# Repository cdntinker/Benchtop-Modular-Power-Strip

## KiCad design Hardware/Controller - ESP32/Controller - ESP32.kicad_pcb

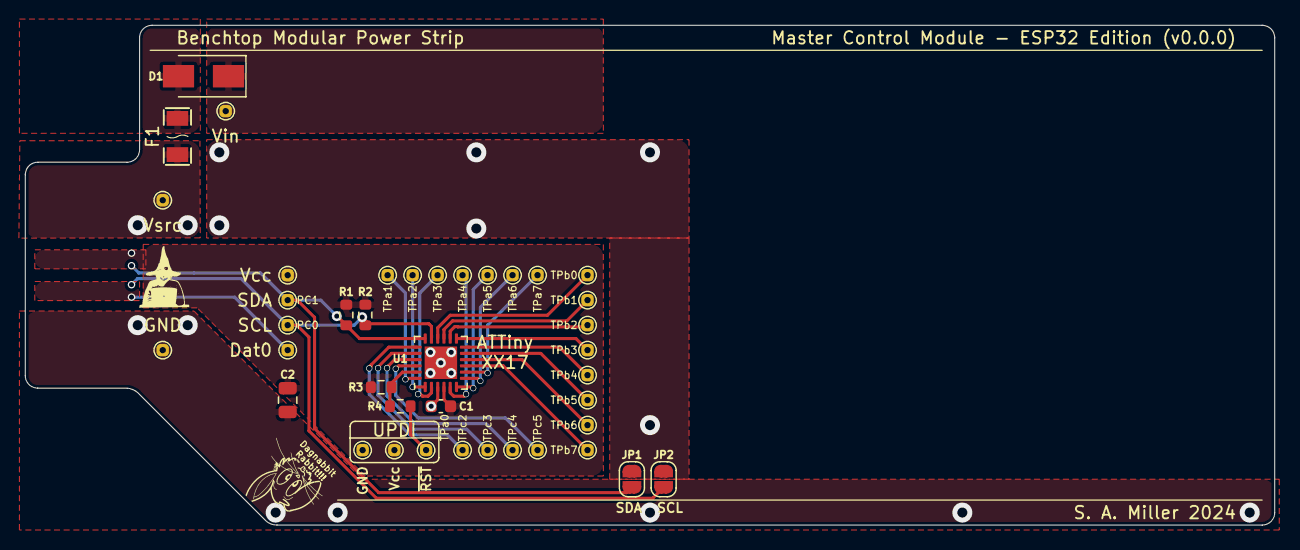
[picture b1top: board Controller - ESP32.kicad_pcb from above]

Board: 2 copper layers, 100.0 x 40.0 mm, 40 parts (0 on the bottom side), 28 nets.

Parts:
C1: 100nF; C_0603_1608Metric
C2: 4.7uF; C_0805_2012Metric
D1: D_Schottky; D_SMA
F1: Polyfuse; F1206
JP1, JP2: SolderJumper_2_Open; SolderJumper-2_P1.3mm_Open_RoundedPad1.0x1.5mm
R1, R2, R3: 10k; R_0603_1608Metric
R4: 330R; R_0603_1608Metric
TP1: Vsrc; TestPoint_THTPad_D1.0mm_Drill0.5mm
TP2, TP9: GND; TestPoint_THTPad_D1.0mm_Drill0.5mm
TP3: Dat0; TestPoint_THTPad_D1.0mm_Drill0.5mm
TP4: Dat1; TestPoint_THTPad_D1.0mm_Drill0.5mm
TP5: Dat2; TestPoint_THTPad_D1.0mm_Drill0.5mm
TP6: Dat3; TestPoint_THTPad_D1.0mm_Drill0.5mm
TP7: Vin; TestPoint_THTPad_D1.0mm_Drill0.5mm
TP8: I2C-Vcc; TestPoint_THTPad_D1.0mm_Drill0.5mm
TPa0: ~{RESET}; TestPoint_THTPad_D1.0mm_Drill0.5mm
TPa1, TPa2, TPa3, TPa4, TPa5, TPa6, TPa7: CtrlA; TestPoint_THTPad_D1.0mm_Drill0.5mm
TPb0, TPb1, TPb2, TPb3, TPb4, TPb5, TPb6, TPb7: CtrlB; TestPoint_THTPad_D1.0mm_Drill0.5mm
TPc2, TPc3, TPc4, TPc5: CtrlC; TestPoint_THTPad_D1.0mm_Drill0.5mm
U1: ATtiny1617; QFN-24-1EP_4x4mm_P0.5mm_EP2.6x2.6mm

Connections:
/ATTinyXX17 Sheet/PA0: R3.2, R4.1, U1.23 (~RESET/PA0)
/ATTinyXX17 Sheet/Vprot: D1.2 (A), F1.2
GND: C1.2, C2.2, TP2.1, TP9.1, U1.3 (GND), U1.25 (GND)
I2C-Vcc: C1.1, C2.1, R1.1, R2.1, R3.1, TP4.1, TP8.1, U1.4 (VCC)
PA1: TPa1.1, U1.24 (PA1)
PA2: TPa2.1, U1.1 (PA2)
PA3: TPa3.1, U1.2 (PA3)
PA4: TPa4.1, U1.5 (PA4)
PA5: TPa5.1, U1.6 (PA5)
PA6: TPa6.1, U1.7 (PA6)
PA7: TPa7.1, U1.8 (PA7)
PB0: TPb0.1, U1.16 (PB0)
PB1: TPb1.1, U1.15 (PB1)
PB2: TPb2.1, U1.14 (PB2)
PB3: TPb3.1, U1.13 (PB3)
PB4: TPb4.1, U1.12 (PB4)
PB5: TPb5.1, U1.11 (PB5)
PB6: TPb6.1, U1.10 (PB6)
PB7: TPb7.1, U1.9 (PB7)
PC2: TPc2.1, U1.19 (PC2)
PC3: TPc3.1, U1.20 (PC3)
PC4: TPc4.1, U1.21 (PC4)
PC5: TPc5.1, U1.22 (PC5)
SCL: JP2.1 (A), R2.2, TP6.1, U1.17 (PC0)
SDA: JP1.1 (A), R1.2, TP5.1, U1.18 (PC1)
Vin: D1.1 (K), TP7.1
Vsrc: F1.1, TP1.1
~RESET: R4.2, TPa0.1

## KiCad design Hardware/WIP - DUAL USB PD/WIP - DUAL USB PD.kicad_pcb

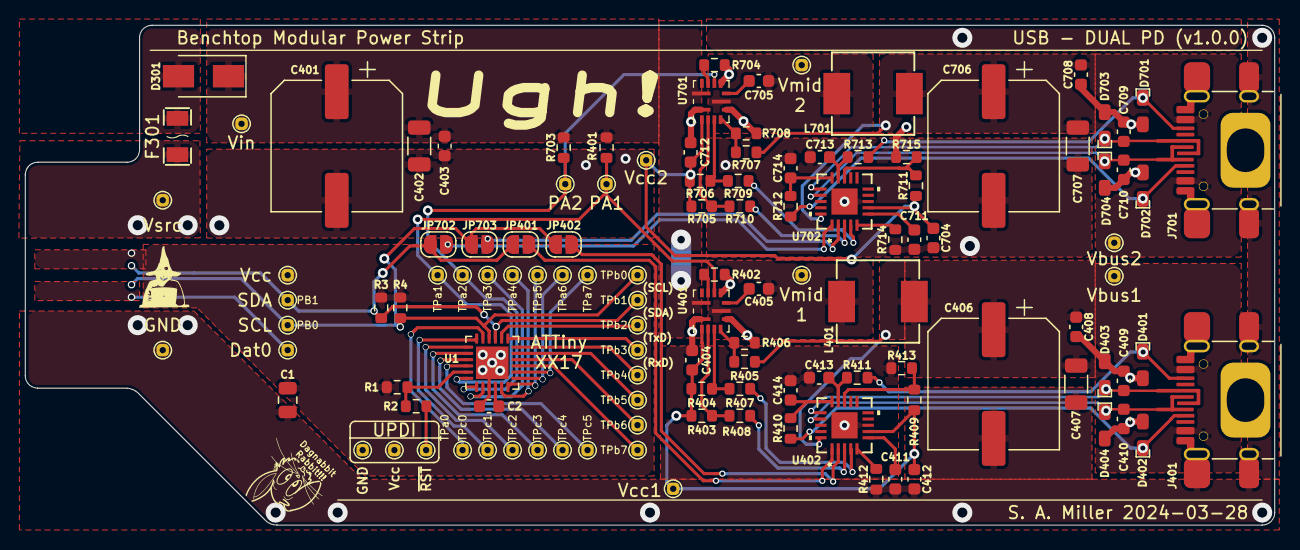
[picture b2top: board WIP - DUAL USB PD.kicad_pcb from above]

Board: 2 copper layers, 100.0 x 40.0 mm, 119 parts (0 on the bottom side), 70 nets.

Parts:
C1: 4.7uF; C_0805_2012Metric
C2, C403, C408, C708: 100nF; C_0603_1608Metric
C401, C406, C706: 330uF; CP_Elec_10x7.7
C402, C407, C707: 10uF; C_1206_3216Metric
C404, C412, C704, C712: 2.2uF; C_0603_1608Metric
C405, C705: 1uF; C_0603_1608Metric
C409, C410, C709, C710: 1nF; C_0603_1608Metric
C411, C711: 470nF; C_0603_1608Metric
C413, C414, C713, C714: 390pF; C_0603_1608Metric
D301: D_Schottky; D_SMA
D401, D402, D403, D404, D701, D702, D703, D704: PGB1010603NR; PGB1010603NRHF
F301: Polyfuse; F1206
J401, J701: USB_C_Receptacle; USB_C
JP401, JP402, JP702, JP703: SolderJumper_2_Open; SolderJumper-2_P1.3mm_Open_RoundedPad1.0x1.5mm
L401, L701: 4.7uH; IND-SMD_L7.1-W6.6
R1, R3, R4, R403, R404, R705, R706: 10k; R_0603_1608Metric
R2: 330R; R_0603_1608Metric
R401, R703: 300k; R_0603_1608Metric
R402, R704: 51k; R_0603_1608Metric
R405, R707: 100k; R_0603_1608Metric
R406, R708: 11k; R_0603_1608Metric
R407, R408, R412, R709, R710, R714: 0; R_0603_1608Metric
R409, R711: 33k; R_0603_1608Metric
R410, R411, R712, R713: 2R2; R_0603_1608Metric
R413, R715: 47k; R_0603_1608Metric
TP1: I2C-Vcc; TestPoint_THTPad_D1.0mm_Drill0.5mm
TP4, TP303: GND; TestPoint_THTPad_D1.0mm_Drill0.5mm
TP5: Dat0; TestPoint_THTPad_D1.0mm_Drill0.5mm
TP6: Dat1; TestPoint_THTPad_D1.0mm_Drill0.5mm
TP7: Dat2; TestPoint_THTPad_D1.0mm_Drill0.5mm
TP8: Dat3; TestPoint_THTPad_D1.0mm_Drill0.5mm
TP301: Vsrc; TestPoint_THTPad_D1.0mm_Drill0.5mm
TP302: Vin; TestPoint_THTPad_D1.0mm_Drill0.5mm
TP401: CtrlA; TestPoint_THTPad_D1.0mm_Drill0.5mm
TP402, TP702: Vmid; TestPoint_THTPad_D1.0mm_Drill0.5mm
TP403, TP703: PD-Vcc; TestPoint_THTPad_D1.0mm_Drill0.5mm
TP404, TP704: Vbus; TestPoint_THTPad_D1.0mm_Drill0.5mm
TP701: CtrlB; TestPoint_THTPad_D1.0mm_Drill0.5mm
TPa0: ~{RESET}; TestPoint_THTPad_D1.0mm_Drill0.5mm
TPa1, TPa2, TPa3, TPa4, TPa5, TPa6, TPa7: CtrlA; TestPoint_THTPad_D1.0mm_Drill0.5mm
TPb0, TPb1, TPb2, TPb3, TPb4, TPb5, TPb6, TPb7: CtrlB; TestPoint_THTPad_D1.0mm_Drill0.5mm
TPc0, TPc1, TPc2, TPc3, TPc4, TPc5: CtrlC; TestPoint_THTPad_D1.0mm_Drill0.5mm
U1: ATtiny1617; QFN-24-1EP_4x4mm_P0.5mm_EP2.6x2.6mm
U401, U701: MP2491CGQB-P; QFN-13_2p5MMx3MM_MNP
U402, U702: MP5031GRE-00A3-P; QFN-20_MP5031_MNP

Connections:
/ATTinyXX17/PA0: R1.2, R2.1, U1.23 (~RESET/PA0)
/Source Power Rail/Vprot: D301.2 (A), F301.2
/USB-PD-2/Vmid2: C705.2, L701.1, TP702.1, U701.8 (SW)
/USB-PD/Vmid: C405.2, L401.1, TP402.1, U401.8 (SW)
CC1: D402.1, J401.A5 (CC1), R410.2
CC1b: D702.1, J701.A5 (CC1), R712.2
CC2: D401.1, J401.B5 (CC2), R411.2
CC2b: D701.1, J701.B5 (CC2), R713.2
D+: C409.1, D403.1, J401.3 (D+), U402.16 (DP)
D-: C410.1, D404.1, J401.2 (D-), U402.17 (DM)
Db+: C709.1, D703.1, J701.3 (D+), U702.16 (DP)
Db-: C710.1, D704.1, J701.2 (D-), U702.17 (DM)
GND: C1.2, C2.2, C401.2, C402.2, C403.2, C404.2, C406.2, C407.2, C408.2, C409.2, C410.2, C411.2, C412.2, C413.2, C414.2, C704.2, C706.2, C707.2, C708.2, C709.2, C710.2, C711.2, C712.2, C713.2, C714.2, D401.2, D402.2, D403.2, D404.2, D701.2, D702.2, D703.2, D704.2, J401.4 (GND), J401.5 (SHIELD), J701.4 (GND), J701.5 (SHIELD), R402.2, R406.2, R412.2, R413.2, R704.2, R708.2, R714.2, R715.2, TP4.1, TP303.1, U1.3 (GND), U1.25 (GND), U401.2 (PGND), U401.7 (AGND), U401.10 (MODE), U402.8 (GND), U402.21 (EPAD), U701.2 (PGND), U701.7 (AGND), U701.10 (MODE), U702.8 (GND), U702.21 (EPAD)
GPIO1: R408.2, U402.3 (GPIO1)
GPIO1b: R710.2, U702.3 (GPIO1)
GPIO5: R407.2, U402.4 (GPIO5)
GPIO5b: R709.2, U702.4 (GPIO5)
I2C-Vcc: C1.1, C2.1, R1.1, R3.1, R4.1, TP1.1, TP6.1, U1.4 (VCC)
unnamed: C405.1, U401.9 (BST)
unnamed: C411.1, U402.6 (VDD)
unnamed: C413.1, R411.1, U402.14 (CC2)
unnamed: C414.1, R410.1, U402.15 (CC1)
unnamed: C705.1, U701.9 (BST)
unnamed: C711.1, U702.6 (VDD)
unnamed: C713.1, R713.1, U702.14 (CC2)
unnamed: C714.1, R712.1, U702.15 (CC1)
unnamed: JP401.2 (B), U402.1 (SDA)
unnamed: JP402.2 (B), U402.2 (SCL)
unnamed: JP702.2 (B), U702.1 (SDA)
unnamed: JP703.2 (B), U702.2 (SCL)
unnamed: R402.1, U401.12 (ILIM)
unnamed: R405.2, R406.1, U401.6 (FB)
unnamed: R409.2, R413.1, U402.13 (NTC)
unnamed: R412.1, U402.5 (I2C_MODE)
unnamed: R704.1, U701.12 (ILIM)
unnamed: R707.2, R708.1, U701.6 (FB)
unnamed: R711.2, R715.1, U702.13 (NTC)
unnamed: R714.1, U702.5 (I2C_MODE)
PA1: R401.2, TP401.1, TPa1.1, U1.24 (PA1), U401.11 (EN)
PA2: R703.2, TP701.1, TPa2.1, U1.1 (PA2), U701.11 (EN)
PA3: TPa3.1, U1.2 (PA3)
PA4: TPa4.1, U1.5 (PA4)
PA5: TPa5.1, U1.6 (PA5)
PA6: TPa6.1, U1.7 (PA6)
PA7: TPa7.1, U1.8 (PA7)
PB0: JP402.1 (A), JP703.1 (A), R4.2, TP8.1, TPb0.1, U1.16 (PB0)
PB1: JP401.1 (A), JP702.1 (A), R3.2, TP7.1, TPb1.1, U1.15 (PB1)
PB2: TPb2.1, U1.14 (PB2)
PB3: TPb3.1, U1.13 (PB3)
PB4: TPb4.1, U1.12 (PB4)
PB5: TPb5.1, U1.11 (PB5)
PB6: TPb6.1, U1.10 (PB6)
PB7: TPb7.1, U1.9 (PB7)
PC0: TPc0.1, U1.17 (PC0)
PC1: TPc1.1, U1.18 (PC1)
PC2: TPc2.1, U1.19 (PC2)
PC3: TPc3.1, U1.20 (PC3)
PC4: TPc4.1, U1.21 (PC4)
PC5: TPc5.1, U1.22 (PC5)
PD-Vcc: C404.1, C412.1, R403.1, R404.1, R409.1, TP403.1, U401.3 (VCC), U402.7 (VCC)
PD-Vccb: C704.1, C712.1, R705.1, R706.1, R711.1, TP703.1, U701.3 (VCC), U702.7 (VCC)
VSEL1: R403.2, R408.1, U401.4 (VSEL1)
VSEL1b: R705.2, R710.1, U701.4 (VSEL1)
VSEL2: R404.2, R407.1, U401.5 (VSEL2)
VSEL2b: R706.2, R709.1, U701.5 (VSEL2)
Vbus1: C406.1, C407.1, C408.1, J401.1 (VBUS), L401.2, R405.1, TP404.1, U402.20 (VBUS_P)
Vbus2: C706.1, C707.1, C708.1, J701.1 (VBUS), L701.2, R707.1, TP704.1, U702.20 (VBUS_P)
Vin: C401.1, C402.1, C403.1, D301.1 (K), R401.1, R703.1, TP302.1, U401.1 (IN), U701.1 (IN)
Vsrc: F301.1, TP301.1
~RESET: R2.2, TPa0.1
